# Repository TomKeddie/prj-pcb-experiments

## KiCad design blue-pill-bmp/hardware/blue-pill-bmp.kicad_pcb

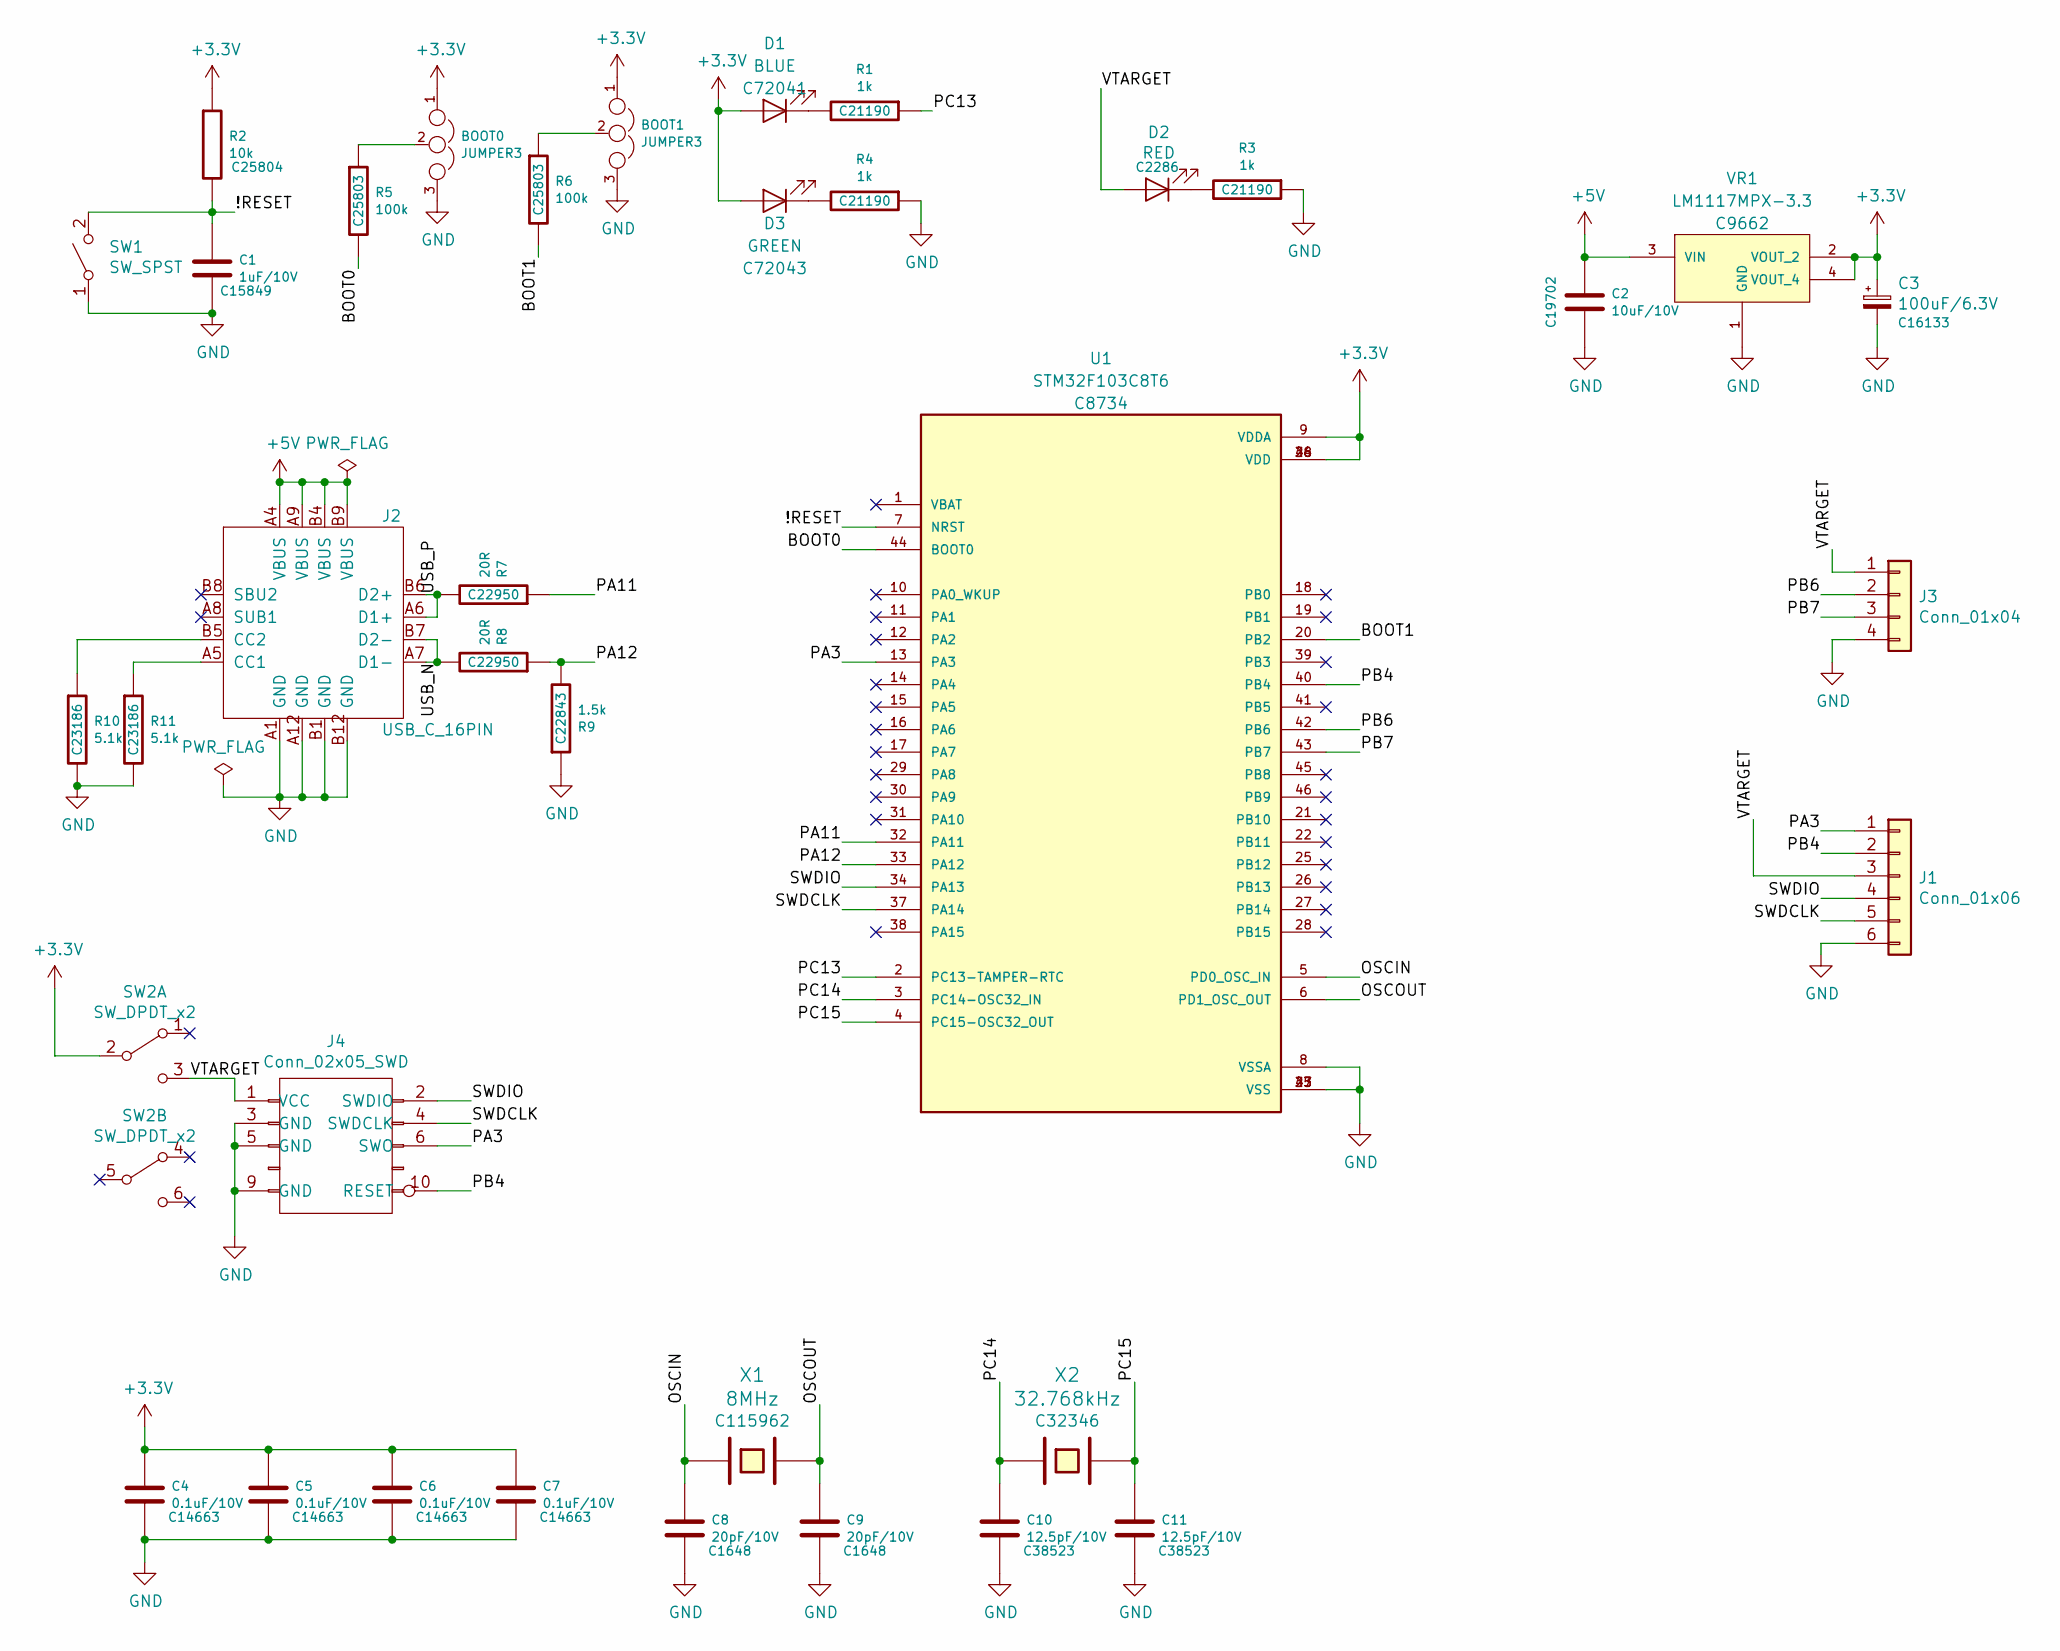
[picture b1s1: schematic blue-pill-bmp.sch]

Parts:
BOOT0, BOOT1: JUMPER3; SolderJumper-3_P2.0mm_Open_TrianglePad1.0x1.5mm; LCSC DNP
C1: 1uF/10V; C_0603_1608Metric; LCSC C15849
C2: 10uF/10V; C_0603_1608Metric; LCSC C19702
C3: 100uF/6.3V; CP_EIA-3528-15_AVX-H; LCSC C16133
C4, C5, C6, C7: 0.1uF/10V; C_0603_1608Metric; LCSC C14663
C8, C9: 20pF/10V; C_0603_1608Metric; LCSC C1648
C10, C11: 12.5pF/10V; C_0603_1608Metric; LCSC C38523
D1: BLUE; LED_0603_1608Metric; LCSC C72041
D2: RED; LED_0603_1608Metric; LCSC C2286
D3: GREEN; LED_0603_1608Metric; LCSC C72043
J1: Conn_01x06; PinHeader_1x06_P2.54mm_Vertical
J2: USB_C_16PIN; USB_C_Receptacle_GT-USB-7010; LCSC DNP
J3: Conn_01x04; PinHeader_1x04_P2.54mm_Vertical; LCSC DNP
J4: Conn_02x05_SWD; PinHeader_2x05_P1.27mm_Vertical; LCSC DNP
R1, R3, R4: 1k; R_0603_1608Metric; LCSC C21190
R2: 10k; R_0603_1608Metric; LCSC C25804
R5, R6: 100k; R_0603_1608Metric; LCSC C25803
R7, R8: 20R; R_0603_1608Metric; LCSC C22950
R9: 1.5k; R_0603_1608Metric; LCSC C22843
R10, R11: 5.1k; R_0603_1608Metric; LCSC C23186
SW1: SW_SPST; SW_Push_1P1T_NO_CK_KMR2; LCSC DNP
SW2: SW_DPDT_x2; SW_DPDT_SMD; LCSC DNP
U1: STM32F103C8T6; QFP50P900X900X160-48N; PARTREV 10; LCSC C8734
VR1: LM1117MPX-3.3; VREG_LM1117MPX-3.3; PARTREV O; LCSC C9662
X1: 8MHz; Crystal_SMD_5032-2Pin_5.0x3.2mm; LCSC C115962
X2: 32.768kHz; Crystal_SMD_5032-2Pin_5.0x3.2mm; LCSC C32346

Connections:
+3V3: BOOT0.1, BOOT1.1, C3.1, C4.1, C5.1, C6.1, C7.1, D1.2 (A), D3.2 (A), R2.1, SW2.2 (B), U1.9 (VDDA), U1.24 (VDD), U1.36 (VDD), U1.48 (VDD), VR1.2 (VOUT_2), VR1.4 (VOUT_4)
+5V: C2.1, J2.A4 (VBUS), J2.A9 (VBUS), J2.B4 (VBUS), J2.B9 (VBUS), VR1.3 (VIN)
/!RESET: C1.1, R2.2, SW1.2 (B), U1.7 (NRST)
/BOOT0: R5.2, U1.44 (BOOT0)
/BOOT1: R6.2, U1.20 (PB2)
/OSCIN: C8.1, U1.5 (PD0_OSC_IN), X1.1
/OSCOUT: C9.1, U1.6 (PD1_OSC_OUT), X1.2
/PA3: J1.1, J4.6 (SWO), U1.13 (PA3)
/PA11: R7.1, U1.32 (PA11)
/PA12: R8.1, R9.2, U1.33 (PA12)
/PB4: J1.2, J4.10 (RESET), U1.40 (PB4)
/PB6: J3.2, U1.42 (PB6)
/PB7: J3.3, U1.43 (PB7)
/PC13: R1.1, U1.2 (PC13-TAMPER-RTC)
/PC14: C10.1, U1.3 (PC14-OSC32_IN), X2.1
/PC15: C11.1, U1.4 (PC15-OSC32_OUT), X2.2
/SWDCLK: J1.5, J4.4 (SWDCLK), U1.37 (PA14)
/SWDIO: J1.4, J4.2 (SWDIO), U1.34 (PA13)
/USB_N: J2.A7 (D1-), J2.B7 (D2-), R8.2
/USB_P: J2.A6 (D1+), J2.B6 (D2+), R7.2
/VTARGET: D2.2 (A), J1.3, J3.1, J4.1 (VCC), SW2.3 (C)
GND: BOOT0.3, BOOT1.3, C1.2, C2.2, C3.2, C4.2, C5.2, C6.2, C7.2, C8.2, C9.2, C10.2, C11.2, J1.6, J2.A1 (GND), J2.A12 (GND), J2.B1 (GND), J2.B12 (GND), J3.4, J4.3 (GND), J4.5 (GND), J4.9 (GND), R3.1, R4.1, R9.1, R10.2, R11.2, SW1.1 (A), U1.8 (VSSA), U1.23 (VSS), U1.35 (VSS), U1.47 (VSS), VR1.1 (GND)
unnamed: BOOT0.2, R5.1
unnamed: BOOT1.2, R6.1
unnamed: D1.1 (K), R1.2
unnamed: D2.1 (K), R3.2
unnamed: D3.1 (K), R4.2
unnamed: J2.A5 (CC1), R11.1
unnamed: J2.B5 (CC2), R10.1

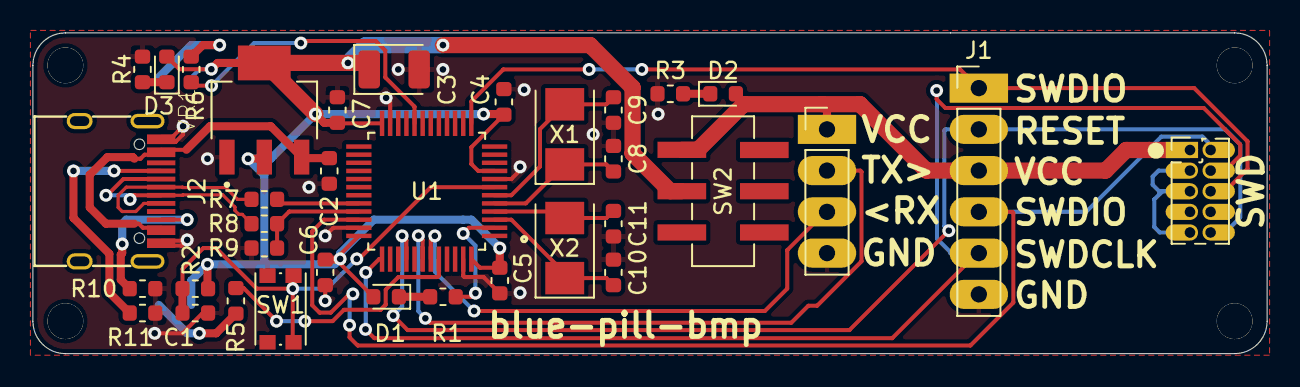
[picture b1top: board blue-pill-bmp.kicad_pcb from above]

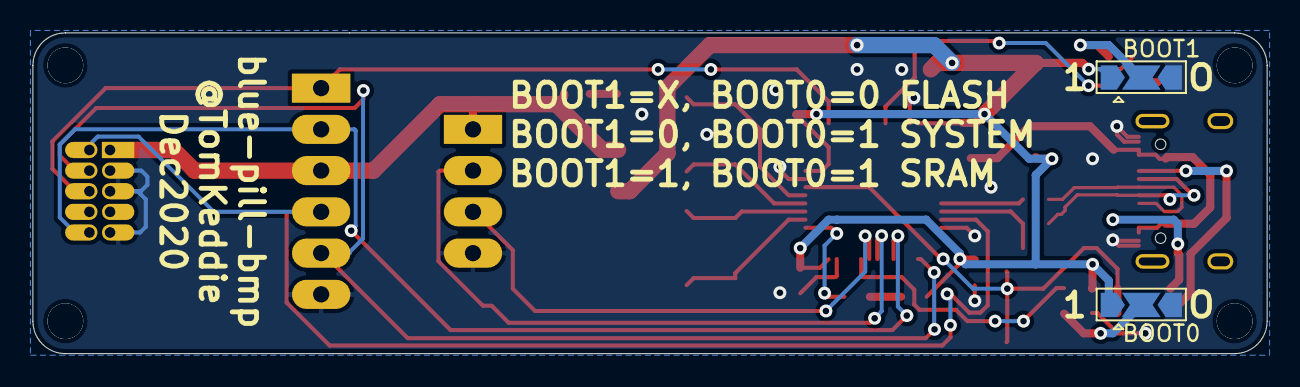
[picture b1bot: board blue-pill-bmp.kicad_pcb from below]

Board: 2 copper layers, 76.0 x 19.8 mm, 37 parts (2 on the bottom side), 29 nets.

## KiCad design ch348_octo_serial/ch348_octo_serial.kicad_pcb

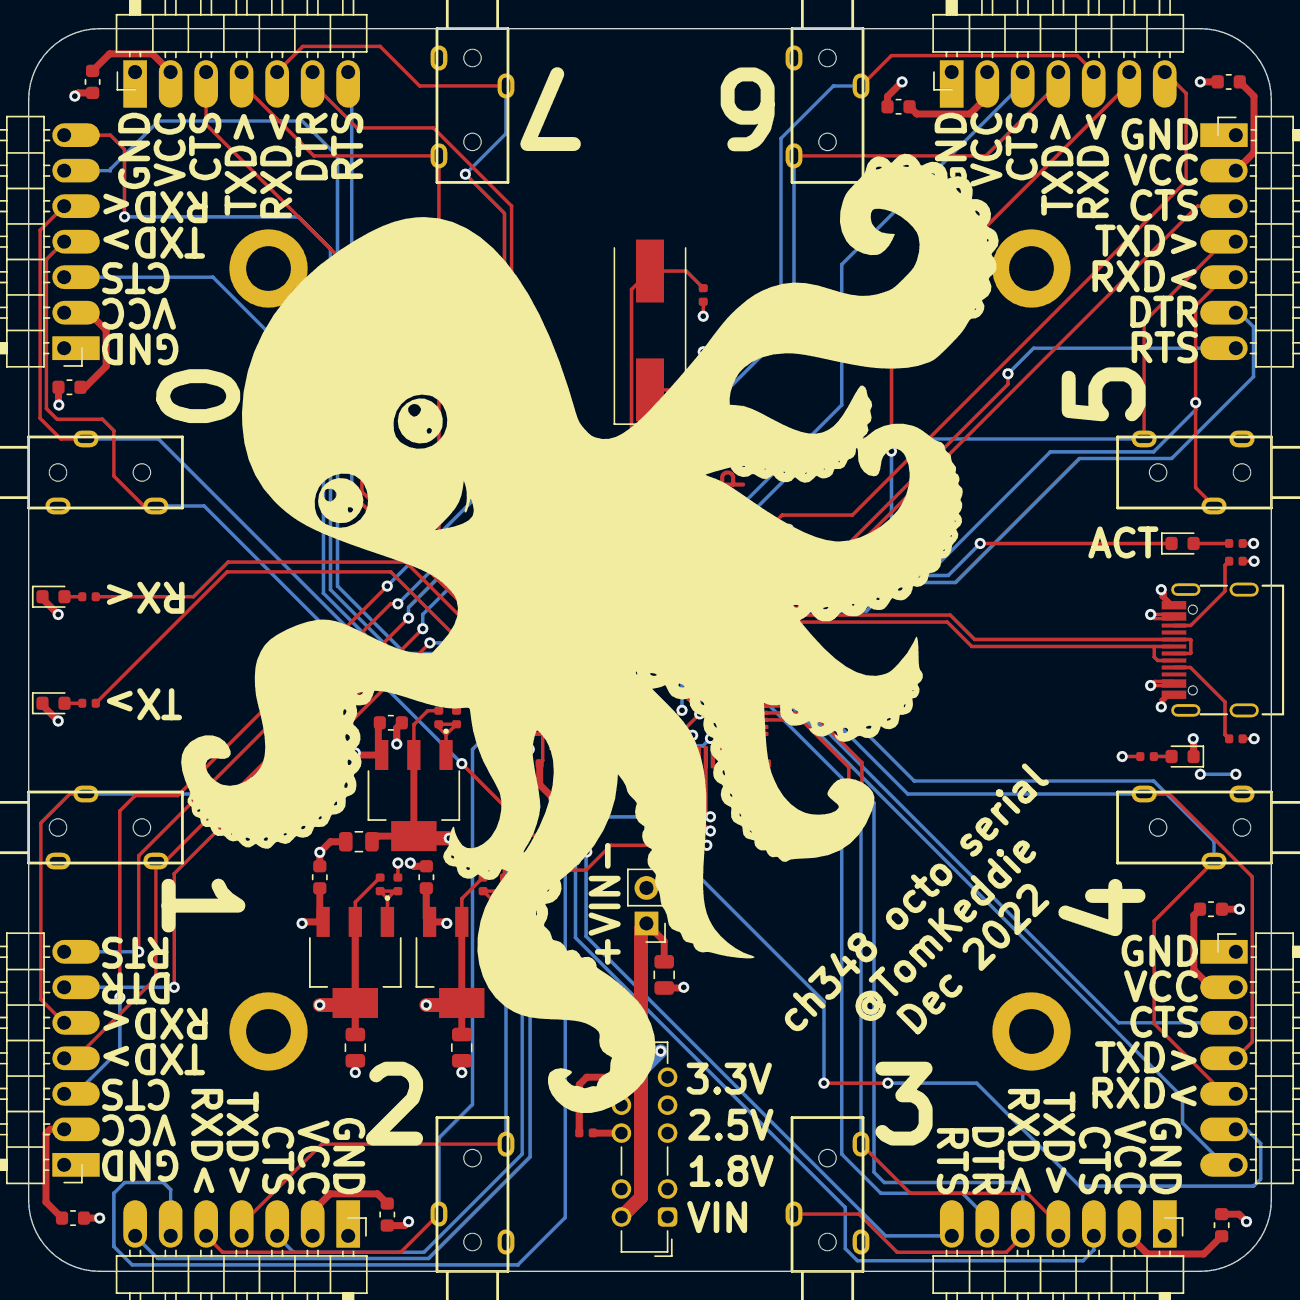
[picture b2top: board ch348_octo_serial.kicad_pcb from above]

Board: 4 copper layers, 88.9 x 88.9 mm, 75 parts (1 on the bottom side), 66 nets.

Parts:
C1, C2, C3: 10uF,25V,X5R; C_0603_1608Metric
C4, C5, C6, C16: 47uF,6.3V,X5R; C_0805_2012Metric
C7, C10, C11, C12, C13, C14, C15, C17: 100nF,16V,X7R; C_0402_1005Metric
C8, C9: 10pF,50V,C0G; C_0402_1005Metric
C18, C19, C20, C21, C22, C23, C24, C25: 10uF,10V,X5R; C_0603_1608Metric
D1: WHITE; LED_0603_1608Metric
D2: BLUE; LED_0603_1608Metric
D3: YELLOW; LED_0603_1608Metric
D4: GREEN; LED_0603_1608Metric
H1: Front Octopus; octopus
H2: Back Octopus; octopus_120
J1: USB_C_Receptacle_USB2.0; USB_C_Receptacle_LCSC_C165948
J2, J3, J4, J5: Conn_01x01; MountingHole_3.2mm_M3_DIN965_Pad
J6: VEXT; PinHeader_1x02_P2.54mm_Vertical
J7, J9, J11, J13, J15, J17, J19, J21: JLCPCB_3.5MM_SOCKET_C18166
J8, J10, J12, J14, J16, J18, J20, J22: Conn_01x07; PinHeader_1x07_P2.54mm_Horizontal_Teardrop
R1, R11, R14, R15: 1k; R_0402_1005Metric
R2: 24k; R_0402_1005Metric
R3: 39k; R_0402_1005Metric
R4, R5: 10k; R_0402_1005Metric
R6: 18k; R_0402_1005Metric
R7: 8.2k; R_0402_1005Metric
R8, R9: 5.1k; R_0402_1005Metric
R10, R12, R13: 4.7k; R_0402_1005Metric
R16: 0; R_0402_1005Metric
SW1: SW_DP4T; SW_ALPS_SSSS224100_DP4T
U1: CH348L; LQFP-100_14x14mm_P0.5mm
VR1, VR2, VR3: LM1117S-ADJ; VREG_LM1117MPX-3.3
X1: 8MHz; Crystal_SMD_HC49-SD

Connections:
+1V8: C6.1, R6.1, SW1.7, VR3.2 (VOUT_2), VR3.4 (VOUT_4)
+2V5: C5.1, R4.1, SW1.9, VR2.2 (VOUT_2), VR2.4 (VOUT_4)
+3.3V: C4.1, C11.1, C13.1, C15.1, R1.1, R2.1, R10.1, R11.1, R16.2, SW1.10, U1.11 (VCC), U1.28 (VCC), U1.75 (VCC), VR1.2 (VOUT_2), VR1.4 (VOUT_4)
+5V: C1.1, C2.1, C3.1, J1.A4 (VBUS), J1.A9 (VBUS), J1.B4 (VBUS), J1.B9 (VBUS), VR1.3 (VIN), VR2.3 (VIN), VR3.3 (VIN)
/ACT: D2.1 (K), U1.29 (ACT)
/CFG: R13.2, U1.7 (CFG)
/RESET: C7.1, R10.2, U1.14 (RESET)
/RX_S: R14.1, U1.77 (RX_S)
/Serial Connector 0/CTS: J16.3, U1.70 (CTS0/GPIO0)
/Serial Connector 0/DTR: J16.6, U1.72 (DTR0/TNOW0/GPIO8)
/Serial Connector 0/RTS: J16.7, U1.71 (RTS0/GPIO1)
/Serial Connector 0/RXD: J15.2 (RING), J16.5, U1.69 (RXD0)
/Serial Connector 0/TXD: J15.4 (TIP), J16.4, U1.68 (TXD0)
/Serial Connector 1/CTS: J18.3, U1.23 (CTS1/GPIO2)
/Serial Connector 1/DTR: J18.6, U1.30 (DTR1/TNOW1/GPIO9)
/Serial Connector 1/RTS: J18.7, U1.24 (RTS1/GPIO3)
/Serial Connector 1/RXD: J17.2 (RING), J18.5, U1.26 (RXD1)
/Serial Connector 1/TXD: J17.4 (TIP), J18.4, U1.25 (TXD1)
/Serial Connector 2/CTS: J20.3, U1.52 (CTS2/GPIO4)
/Serial Connector 2/DTR: J20.6, U1.67 (DTR2/TNOW2/GPIO10)
/Serial Connector 2/RTS: J20.7, U1.53 (RTS2/GPIO5)
/Serial Connector 2/RXD: J19.2 (RING), J20.5, U1.48 (RXD2)
/Serial Connector 2/TXD: J19.4 (TIP), J20.4, U1.47 (TXD2)
/Serial Connector 3/CTS: J22.3, U1.51 (CTS3/GPIO6)
/Serial Connector 3/DTR: J22.6, U1.89 (DTR3/TNOW3/GPIO11)
/Serial Connector 3/RTS: J22.7, U1.54 (RTS3/GPIO7)
/Serial Connector 3/RXD: J21.2 (RING), J22.5, U1.79 (RXD3)
/Serial Connector 3/TXD: J21.4 (TIP), J22.4, U1.78 (TXD3)
/Serial Connector 4/CTS: J8.3, U1.90 (CTS4/GPIO12)
/Serial Connector 4/DTR: J8.6, U1.63 (DTR4/TNOW4/GPIO20)
/Serial Connector 4/RTS: J8.7, U1.91 (RTS4/GPIO13)
/Serial Connector 4/RXD: J7.2 (RING), J8.5, U1.83 (RXD4)
/Serial Connector 4/TXD: J7.4 (TIP), J8.4, U1.80 (TXD4)
/Serial Connector 5/CTS: J10.3, U1.95 (CTS5/GPIO14)
/Serial Connector 5/DTR: J10.6, U1.64 (DTR5/TNOW5/GPIO21)
/Serial Connector 5/RTS: J10.7, U1.96 (RTS5/GPIO15)
/Serial Connector 5/RXD: J9.2 (RING), J10.5, U1.16 (RXD5)
/Serial Connector 5/TXD: J9.4 (TIP), J10.4, U1.15 (TXD5)
/Serial Connector 6/CTS: J12.3, U1.31 (CTS6/GPIO16)
/Serial Connector 6/DTR: J12.6, U1.65 (DTR6/TNOW6/GPIO22)
/Serial Connector 6/RTS: J12.7, U1.32 (RTS6/GPIO17)
/Serial Connector 6/RXD: J11.2 (RING), J12.5, U1.18 (RXD6)
/Serial Connector 6/TXD: J11.4 (TIP), J12.4, U1.17 (TXD6)
/Serial Connector 7/CTS: J14.3, U1.35 (CTS7/GPIO18)
/Serial Connector 7/DTR: J14.6, U1.66 (DTR7/TNOW7/GPIO23)
/Serial Connector 7/RTS: J14.7, U1.36 (RTS7/GPIO19)
/Serial Connector 7/RXD: J13.2 (RING), J14.5, U1.34 (RXD7)
/Serial Connector 7/TXD: J13.4 (TIP), J14.4, U1.33 (TXD7)
/TEST: R12.2, U1.94 (TEST)
/TX_S: R15.1, U1.76 (TX_S)
/USB_N: J1.A7 (D-), J1.B7 (D-), U1.92 (USB_N)
/USB_P: J1.A6 (D+), J1.B6 (D+), U1.93 (USB_P)
/XI: C8.1, U1.12 (XI), X1.1
/XO: C9.1, U1.13 (XO), X1.2
GND: C1.2, C2.2, C3.2, C4.2, C5.2, C6.2, C7.2, C8.2, C9.2, C10.2, C11.2, C12.2, C13.2, C14.2, C15.2, C16.2, C17.2, C18.2, C19.2, C20.2, C21.2, C22.2, C23.2, C24.2, C25.2, D1.1 (K), D3.1 (K), D4.1 (K), J1.A1 (GND), J1.A12 (GND), J1.B1 (GND), J1.B12 (GND), J1.S1 (SHIELD), J6.2, J7.3 (SLEEVE), J8.1, J9.3 (SLEEVE), J10.1, J11.3 (SLEEVE), J12.1, J13.3 (SLEEVE), J14.1, J15.3 (SLEEVE), J16.1, J17.3 (SLEEVE), J18.1, J19.3 (SLEEVE), J20.1, J21.3 (SLEEVE), J22.1, R3.2, R5.2, R7.2, R8.2, R9.1, R12.1, R13.1, U1.10 (GND), U1.19 (GND), U1.20 (GND), U1.27 (GND), U1.37 (GND), U1.49 (GND), U1.74 (GND), U1.99 (GND)
unnamed: C16.1, J6.1, SW1.6
unnamed: D1.2 (A), R1.2
unnamed: D2.2 (A), R11.2
unnamed: D3.2 (A), R14.2
unnamed: D4.2 (A), R15.2
unnamed: J1.A5 (CC1), R8.1
unnamed: J1.B5 (CC2), R9.2
unnamed: R2.2, R3.1, VR1.1 (GND)
unnamed: R4.2, R5.1, VR2.1 (GND)
unnamed: R6.2, R7.1, VR3.1 (GND)
Vdrive: C10.1, C12.1, C14.1, C17.1, C18.1, C19.1, C20.1, C21.1, C22.1, C23.1, C24.1, C25.1, J8.2, J10.2, J12.2, J14.2, J16.2, J18.2, J20.2, J22.2, R16.1, SW1.8, U1.21 (VIO), U1.22 (VIO), U1.50 (VIO), U1.100 (VIO)

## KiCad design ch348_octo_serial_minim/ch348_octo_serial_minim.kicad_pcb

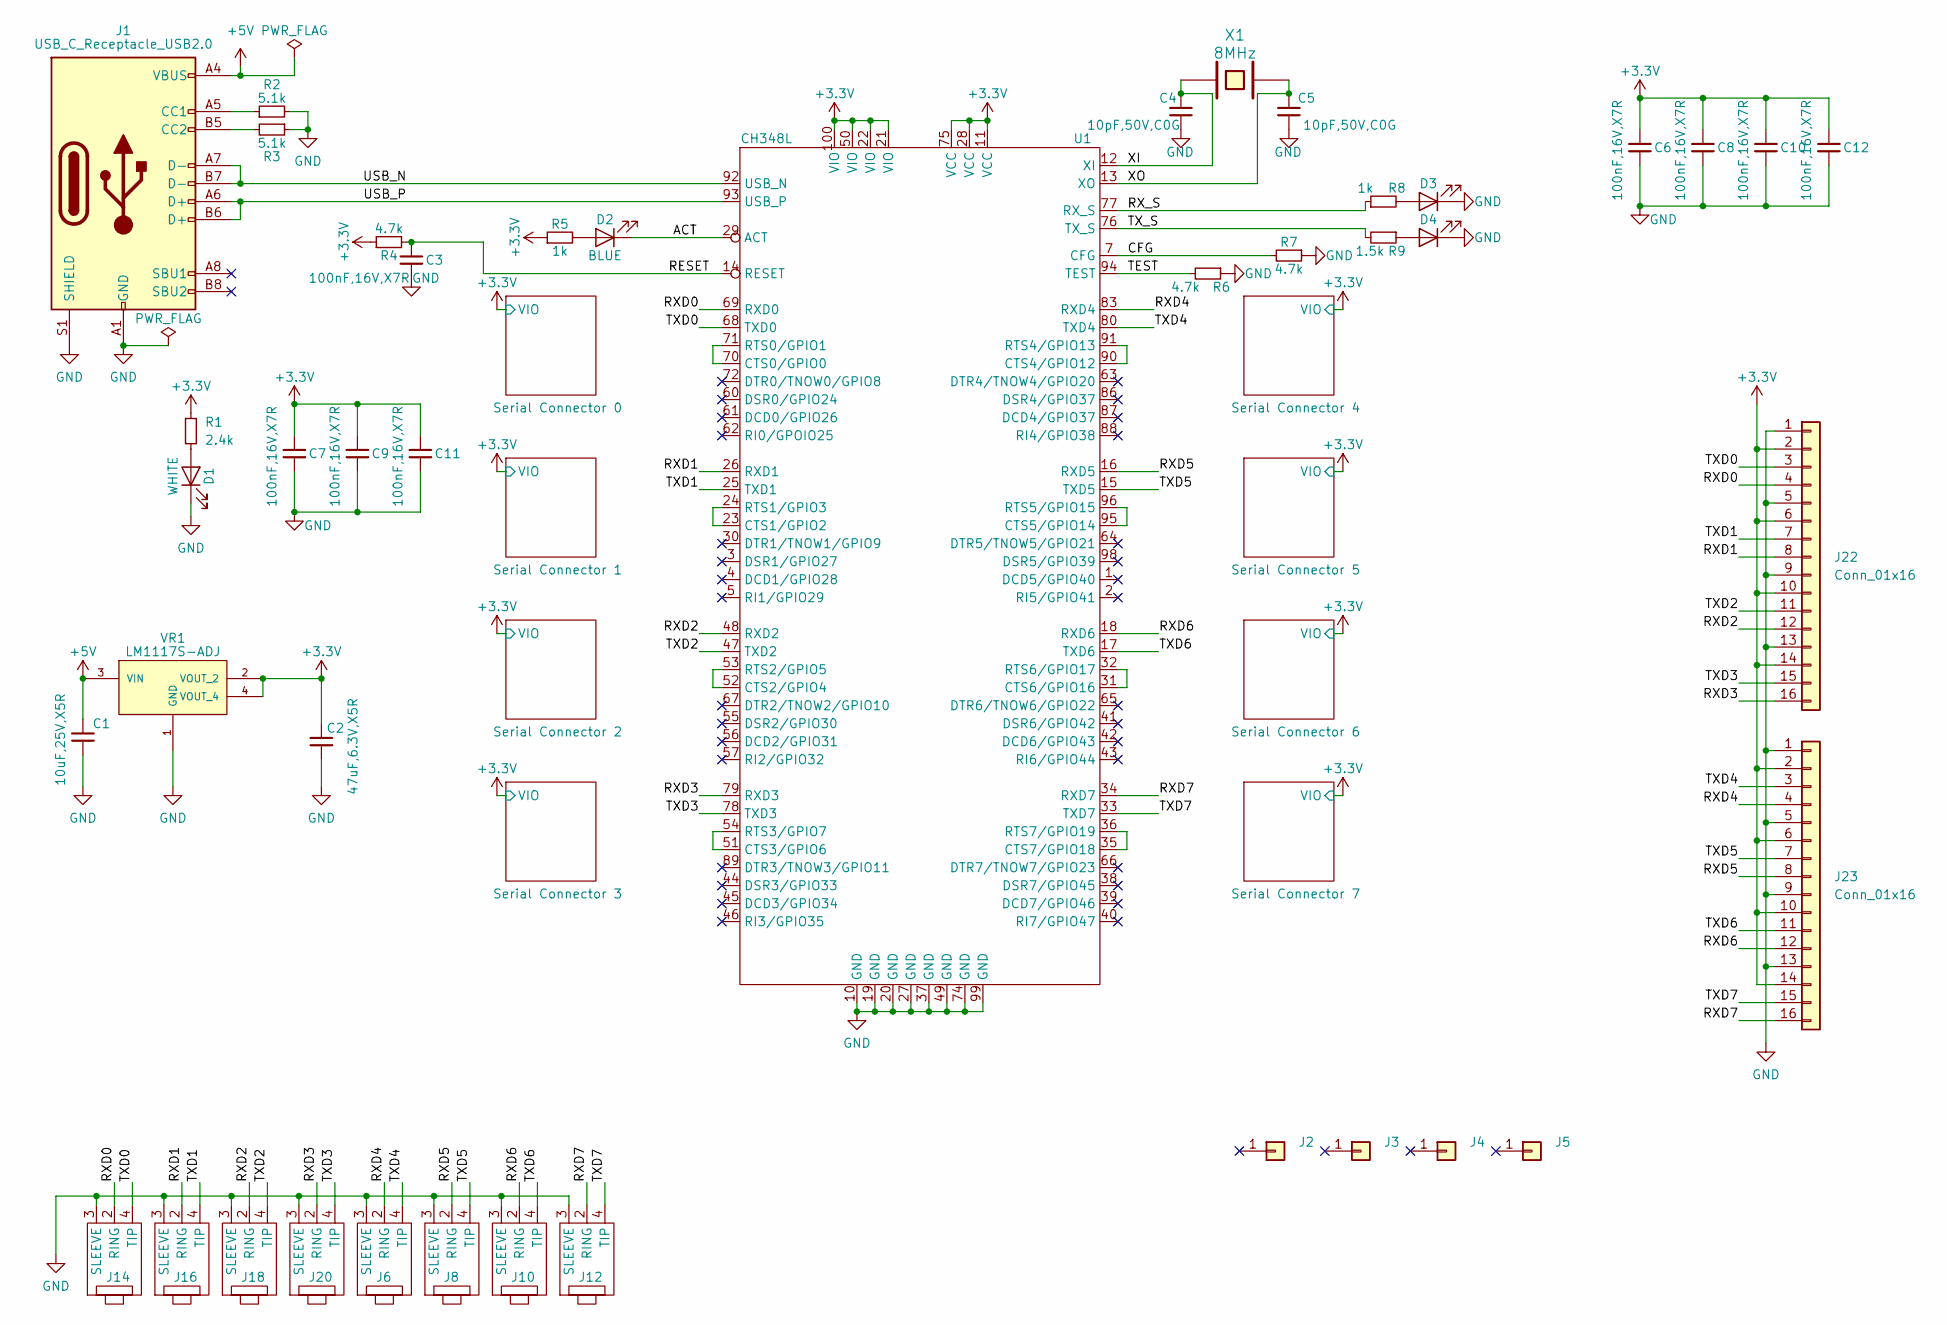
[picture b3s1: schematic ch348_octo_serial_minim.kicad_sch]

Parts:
C1: 10uF,25V,X5R; C_0603_1608Metric; MFGPN CL10A106MA8NRNC; LCSC C96446
C2: 47uF,6.3V,X5R; C_0805_2012Metric; MFGPN CL21A476MQYNNNE; LCSC C16780
C3, C6, C7, C8, C9, C10, C11, C12: 100nF,16V,X7R; C_0402_1005Metric; MFGPN CL05B104KO5NNNC; LCSC C1525
C4, C5: 10pF,50V,C0G; C_0402_1005Metric; MFGPN CL05C100JB5NNNC; LCSC C32949
D1: WHITE; LED_0603_1608Metric; LCSC C2290
D2: BLUE; LED_0603_1608Metric; LCSC C72041
D3: YELLOW; LED_0603_1608Metric; LCSC C72038
D4: GREEN; LED_0603_1608Metric; LCSC C72043
J1: USB_C_Receptacle_USB2.0; USB_C_Receptacle_LCSC_C165948; LCSC C709357
J2, J3, J4, J5: Conn_01x01; MountingHole_3.2mm_M3_DIN965_Pad
J6, J8, J10, J12, J14, J16, J18, J20: JLCPCB_3.5MM_SOCKET_C18166; MPN PJ-3200; LCSC C18166
J22, J23: Conn_01x16; PinHeader_1x16_P2.54mm_Horizontal; LCSC C725908
R1: 2.4k; R_0402_1005Metric; MFGPN 0402WGF2401TCE; LCSC C25882
R2, R3: 5.1k; R_0402_1005Metric; MFGPN 0402WGF5101TCE; LCSC C25905
R4, R6, R7: 4.7k; R_0402_1005Metric; MFGPN 0402WGF4701TCE; LCSC C25900
R5, R8: 1k; R_0402_1005Metric; MFGPN 0402WGF1001TCE; LCSC C11702
R9: 1.5k; R_0402_1005Metric; MFGPN 0402WGF1501TCE; LCSC C25867
U1: CH348L; LQFP-100_14x14mm_P0.5mm; LCSC C2979160
VR1: LM1117S-ADJ; VREG_LM1117MPX-3.3; PARTREV O; LCSC C9662
X1: 8MHz; Crystal_SMD_HC49-SD; LCSC C12674

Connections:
+3.3V: C2.1, C6.1, C7.1, C8.1, C9.1, C10.1, C11.1, C12.1, J22.2, J22.6, J22.10, J22.14, J23.2, J23.6, J23.10, J23.14, R1.1, R4.1, R5.1, U1.11 (VCC), U1.21 (VIO), U1.22 (VIO), U1.28 (VCC), U1.50 (VIO), U1.75 (VCC), U1.100 (VIO), VR1.2 (VOUT_2), VR1.4 (VOUT_4); also elsewhere on the board
+5V: C1.1, J1.A4 (VBUS), J1.A9 (VBUS), J1.B4 (VBUS), J1.B9 (VBUS), VR1.3 (VIN)
/ACT: D2.1 (K), U1.29 (ACT)
/CFG: R7.2, U1.7 (CFG)
/RESET: C3.1, R4.2, U1.14 (RESET)
/RXD0: J14.2 (RING), J22.4, U1.69 (RXD0)
/RXD1: J16.2 (RING), J22.8, U1.26 (RXD1)
/RXD2: J18.2 (RING), J22.12, U1.48 (RXD2)
/RXD3: J20.2 (RING), J22.16, U1.79 (RXD3)
/RXD4: J6.2 (RING), J23.4, U1.83 (RXD4)
/RXD5: J8.2 (RING), J23.8, U1.16 (RXD5)
/RXD6: J10.2 (RING), J23.12, U1.18 (RXD6)
/RXD7: J12.2 (RING), J23.16, U1.34 (RXD7)
/RX_S: R8.1, U1.77 (RX_S)
/TEST: R6.2, U1.94 (TEST)
/TXD0: J14.4 (TIP), J22.3, U1.68 (TXD0)
/TXD1: J16.4 (TIP), J22.7, U1.25 (TXD1)
/TXD2: J18.4 (TIP), J22.11, U1.47 (TXD2)
/TXD3: J20.4 (TIP), J22.15, U1.78 (TXD3)
/TXD4: J6.4 (TIP), J23.3, U1.80 (TXD4)
/TXD5: J8.4 (TIP), J23.7, U1.15 (TXD5)
/TXD6: J10.4 (TIP), J23.11, U1.17 (TXD6)
/TXD7: J12.4 (TIP), J23.15, U1.33 (TXD7)
/TX_S: R9.2, U1.76 (TX_S)
/USB_N: J1.A7 (D-), J1.B7 (D-), U1.92 (USB_N)
/USB_P: J1.A6 (D+), J1.B6 (D+), U1.93 (USB_P)
/XI: C4.1, U1.12 (XI), X1.1
/XO: C5.1, U1.13 (XO), X1.2
GND: C1.2, C2.2, C3.2, C4.2, C5.2, C6.2, C7.2, C8.2, C9.2, C10.2, C11.2, C12.2, D1.1 (K), D3.1 (K), D4.1 (K), J1.A1 (GND), J1.A12 (GND), J1.B1 (GND), J1.B12 (GND), J1.S1 (SHIELD), J6.3 (SLEEVE), J8.3 (SLEEVE), J10.3 (SLEEVE), J12.3 (SLEEVE), J14.3 (SLEEVE), J16.3 (SLEEVE), J18.3 (SLEEVE), J20.3 (SLEEVE), J22.1, J22.5, J22.9, J22.13, J23.1, J23.5, J23.9, J23.13, R2.2, R3.1, R6.1, R7.1, U1.10 (GND), U1.19 (GND), U1.20 (GND), U1.27 (GND), U1.37 (GND), U1.49 (GND), U1.74 (GND), U1.99 (GND), VR1.1 (GND); also elsewhere on the board
unnamed: D1.2 (A), R1.2
unnamed: D2.2 (A), R5.2
unnamed: D3.2 (A), R8.2
unnamed: D4.2 (A), R9.1
unnamed: J1.A5 (CC1), R2.1
unnamed: J1.B5 (CC2), R3.2
unnamed: U1.23 (CTS1/GPIO2), U1.24 (RTS1/GPIO3)
unnamed: U1.31 (CTS6/GPIO16), U1.32 (RTS6/GPIO17)
unnamed: U1.35 (CTS7/GPIO18), U1.36 (RTS7/GPIO19)
unnamed: U1.51 (CTS3/GPIO6), U1.54 (RTS3/GPIO7)
unnamed: U1.52 (CTS2/GPIO4), U1.53 (RTS2/GPIO5)
unnamed: U1.70 (CTS0/GPIO0), U1.71 (RTS0/GPIO1)
unnamed: U1.90 (CTS4/GPIO12), U1.91 (RTS4/GPIO13)
unnamed: U1.95 (CTS5/GPIO14), U1.96 (RTS5/GPIO15)

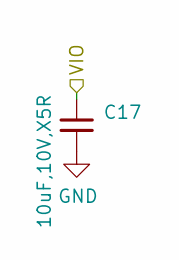
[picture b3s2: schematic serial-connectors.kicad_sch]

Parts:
C17: 10uF,10V,X5R; C_0603_1608Metric; MFGPN CL10A106KP8NNNC; LCSC C19702

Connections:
+3.3V: C17.1; also elsewhere on the board
GND: C17.2; also elsewhere on the board

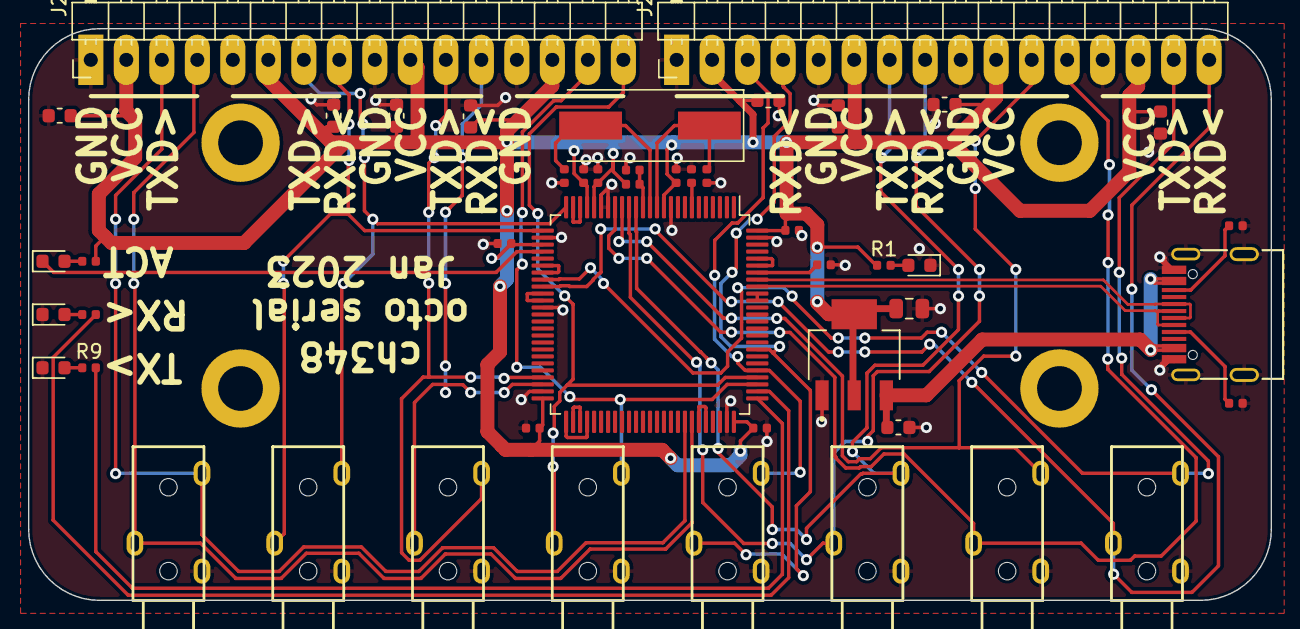
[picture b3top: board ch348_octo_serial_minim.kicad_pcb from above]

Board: 2 copper layers, 88.9 x 40.9 mm, 51 parts (0 on the bottom side), 43 nets.

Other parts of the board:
C13, C14, C15, C16, C18, C19, C20: 10uF,10V,X5R; C_0603_1608Metric

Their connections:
+3.3V: C13.1, C14.1, C15.1, C16.1, C18.1, C19.1, C20.1; also elsewhere on the board
GND: C13.2, C14.2, C15.2, C16.2, C18.2, C19.2, C20.2; also elsewhere on the board

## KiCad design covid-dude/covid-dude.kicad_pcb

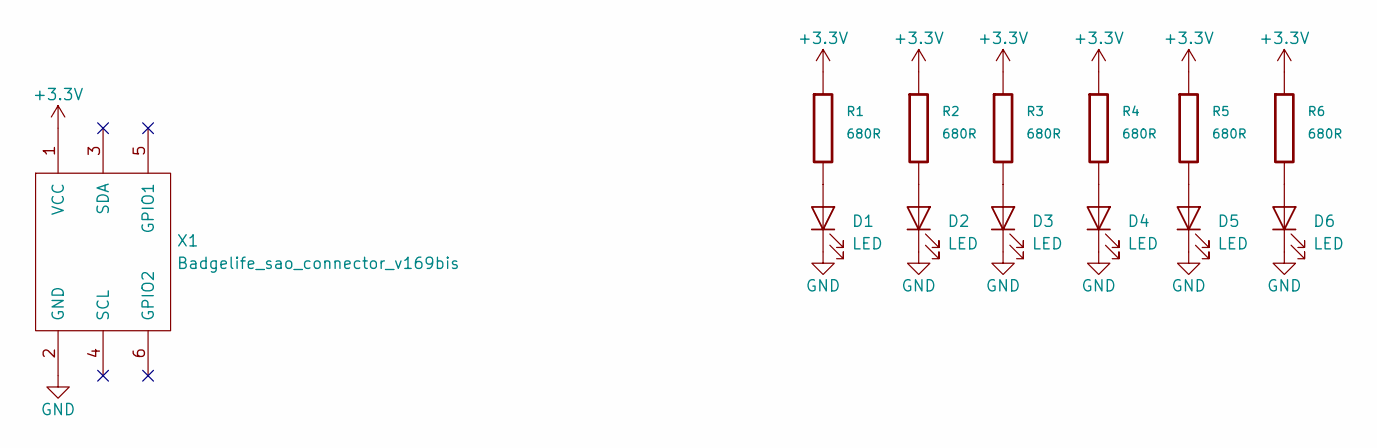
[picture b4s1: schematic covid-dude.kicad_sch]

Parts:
D1, D2, D3, D4, D5, D6: LED; ALIEXPRESS_LED_SIDE_1204
R1, R2, R3, R4, R5, R6: 680R; C_0805_2012Metric_Pad1.15x1.40mm_HandSolder; LCSC DNP
X1: Badgelife_sao_connector_v169bis; Badgelife-SAOv169-SAO-2x3-SMD-BIGPADS

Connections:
+3.3V: R1.1, R2.1, R3.1, R4.1, R5.1, R6.1, X1.1 (VCC)
GND: D1.1 (K), D2.1 (K), D3.1 (K), D4.1 (K), D5.1 (K), D6.1 (K), X1.2 (GND)
unnamed: D1.2 (A), R1.2
unnamed: D2.2 (A), R2.2
unnamed: D3.2 (A), R3.2
unnamed: D4.2 (A), R4.2
unnamed: D5.2 (A), R5.2
unnamed: D6.2 (A), R6.2

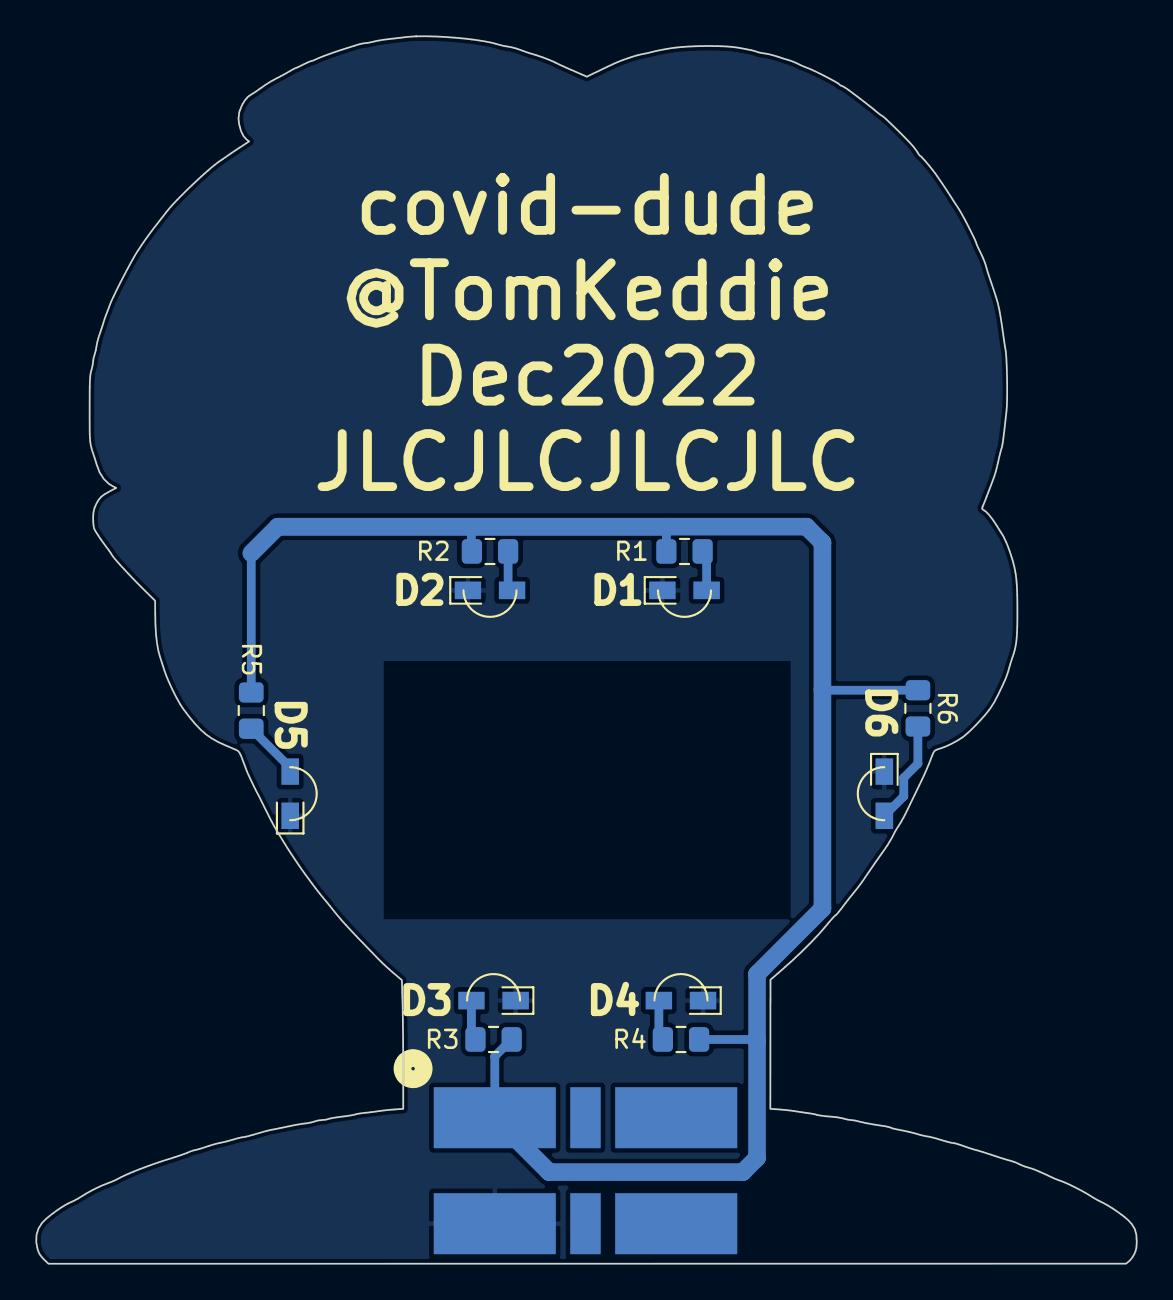
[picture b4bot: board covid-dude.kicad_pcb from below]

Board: 2 copper layers, 62.2 x 69.4 mm, 13 parts (13 on the bottom side), 8 nets.
